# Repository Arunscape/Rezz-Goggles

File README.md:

# [WIP] An attempt at making my own pair of Rezz Goggles
###### Why? For fun.

###### For now, the readme will be documenting my progress

## Materials list:
###### These are the parts I have on hand and what I think I will use
- 8x [SK6812RGBW LEDs](https://www.adafruit.com/product/2761) (I have 10 just in case)
- 2x [24 LED rings](https://www.adafruit.com/product/2862)
- 2x [16 LED rings](https://www.adafruit.com/product/2862)
- [adafruit trinket m0](https://www.adafruit.com/product/3500) or [gemma m0](https://www.adafruit.com/product/3501) or feather [huzzah](https://www.adafruit.com/product/3046)
  - For now, I will be using the gemma

## Datasheets
- https://cdn-shop.adafruit.com/datasheets/WS2812.pdf
- https://cdn-shop.adafruit.com/product-files/1138/SK6812+LED+datasheet+.pdf
- https://cdn-shop.adafruit.com/product-files/2757/p2757_SK6812RGBW_REV01.pdf

## Documentation
- FastLED Library https://github.com/FastLED/FastLED/wiki/Overview

# Current challenges:
- I have a friend willing to help design the surface mount PCB for the LEDs in the centre
- Powering the LEDs
  - [adafruit guide](https://learn.adafruit.com/adafruit-neopixel-uberguide/powering-neopixels)
  - ~~I'm leaning towards using 4x AA NiMH batteries or 3x AA Alkalines~~
  - ~~using NiMH will have an upfront cost of like $50. Alternatively,~~
  I can just use some Alkaline AAs and just get a battery holder + JST connectors
  - ~~I'll buy a 1000uF capacitor. There's one on digikey with a rating for 10V~~
  - Looks like 3x AA batteries are the way to go. no capacitor needed
  - this looks like a cool battery holder https://www.adafruit.com/product/3287
- 3D printing the glasses frame
  - Probably search for a .stl somewhere
  - figure out which CAD software to use - ask fren for help
  - prototype from that .stl -> need to figure out how to fit over prescription glasses

## Random notes:
- Use a 300-500 ohm resistor to data in of the first neopixel

## Random thoughts
- The feather huzzah would be interesting, since I theoretically could control the system with my phone, but that would result in a huge hit to battery life. I'll stick to using the gemma for now
- I need to find an appropriate battery to use plus the JST connector
- The internet suggests that the [fastLED](http://fastled.io/) library is much better than adafruit's [neopixel library](https://github.com/adafruit/Adafruit_NeoPixel)
- it would be cool if I could get my hands on a microphone to see if I can make an effect that reacts to surrounding frequencies. That would be tacked when I'm nearly finished the project
- maybe I want a multimeter

## Reference images

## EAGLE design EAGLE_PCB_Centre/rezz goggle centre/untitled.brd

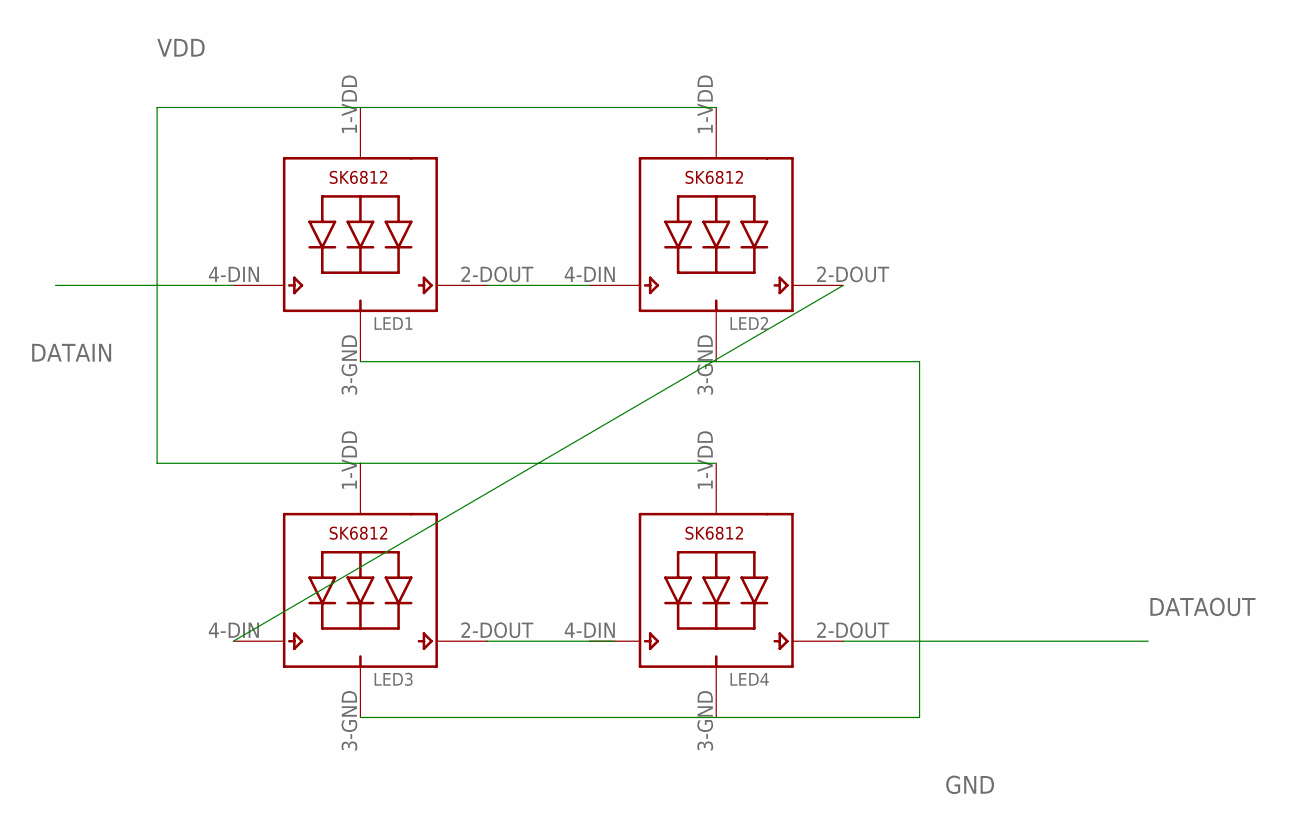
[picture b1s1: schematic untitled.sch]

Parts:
LED1, LED2, LED3, LED4: SK6812_5050W; LED5050_W

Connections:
DATAIN: LED1.4-DIN (DI)
DATAOUT: LED4.2-DOUT (DO)
GND: LED1.3-GND (GND), LED2.3-GND (GND), LED3.3-GND (GND), LED4.3-GND (GND)
unnamed: LED1.2-DOUT (DO), LED2.4-DIN (DI)
unnamed: LED2.2-DOUT (DO), LED3.4-DIN (DI)
VDD: LED1.1-VDD (VDD), LED2.1-VDD (VDD), LED3.1-VDD (VDD), LED4.1-VDD (VDD)

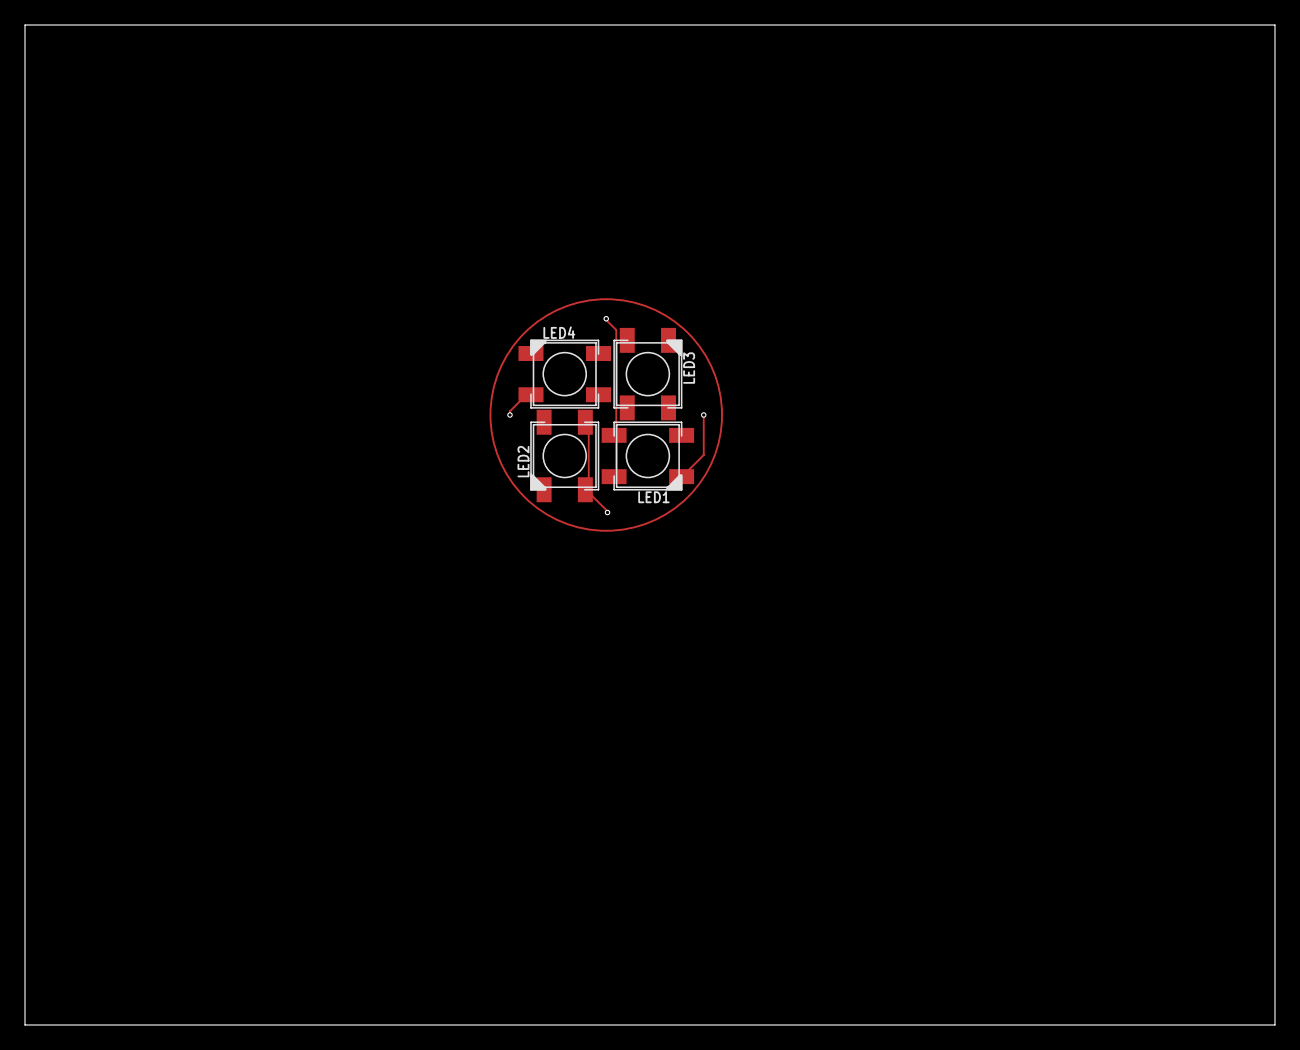
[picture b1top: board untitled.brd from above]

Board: 2 copper layers, 100.0 x 80.0 mm, 4 parts (0 on the bottom side), 4 nets.

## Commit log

2019-01-02 readme
2019-01-02 project setup
2019-01-02 random thought
2019-01-04 naive pcb design for the centre LEDs
